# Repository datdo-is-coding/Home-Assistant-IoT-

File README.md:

# HomeCompetition

Ứng dụng Firebase, Gateway Pi4 và các Box ESP32-S3. Bản đồ nguồn đã rà soát ngày
2026-10-28:

| Thành phần | Nguồn duy trì | Điểm vào |
| --- | --- | --- |
| App duy nhất | `App/HomeCompetition/` | `lib/main.dart` → `FirebaseHomeClient` |
| Web Dashboard | `Web/iot_dashboard/` | `app.py` / `lib/main.dart` |
| Gateway chính | `Gateway/gateway/` | `main.py`, cầu nối `firebase_commissioning.py` |
| Đăng ký/quyền/kênh/lệnh Core | `Gateway/gateway/core_v1/` | Registry SQLite, provisioning, command queue |
| OTA đã ký | `Gateway/gateway/fleet_ota/` | `python -m gateway.fleet_ota.local` cho pilot Pi |
| ActionBox 3 relay / 3 BL0942 | `Firmware/firmware_esp/ActionBox_V2/` | `src/main.cpp` |
| SubBox điều phối / âm thanh | `Firmware/firmware_esp/SubBox/` | `src/main.cpp` |
| Giao thức/OTA/bảo mật chung | `Firmware/firmware_esp/common/hc_core/` | Component ESP-IDF của cả hai Box |
| Giọng nói đang dùng | `Gateway/gateway/asr_engine.py`, `core_v1/speaker_voice.py` | Pi4 nhận PCM, ASR, lệnh Core và phản hồi; WakeNet ở ActionBox |
| Model/MFCC KWS đã dừng | `Firmware/firmware_esp/common/kws/` | Giữ lịch sử; không build/chạy LocalKws trên SubBox |

Thông tin đang chạy và các phần chưa nối xong nằm trong
[trạng thái hệ thống](docs/architecture/current_state.md). Bản phát hành đã giữ ở
[`releases/`](releases/README.md). Bản sao cũ, công cụ demo, dữ liệu huấn luyện đã
dừng và build/cache dư nằm trong
[`archive/2026-10-28-cleanup/`](archive/2026-10-28-cleanup/README.md), kèm manifest
hash và vị trí gốc. Archive giữ dữ liệu để phục hồi, không giảm dung lượng đĩa.

## App

```sh
cd App/HomeCompetition
flutter pub get
flutter analyze
flutter test --concurrency=1
flutter build apk --release
```

Giữ Android application ID đã đăng ký Firebase. Sau khi đổi nhánh hoặc khôi phục
cache, chạy `flutter pub get` để tạo lại phần đăng ký native plugin. Xem
[hướng dẫn app](App/HomeCompetition/README.md).

## Web Dashboard

Ứng dụng web dashboard và server Flask phục vụ giao diện:

```sh
cd Web/iot_dashboard
python3 app.py
# Hoặc chạy trực tiếp Flutter Web:
# flutter run -d chrome
```

## Firmware

Trong môi trường ESP-IDF 6.0.2 đã kích hoạt, từ gốc repo:

```sh
idf.py -C Firmware/firmware_esp/ActionBox_V2 build
idf.py -C Firmware/firmware_esp/SubBox build
```

`managed_components/`, `dependencies.lock`, `sdkconfig` và `sdkconfig.defaults`
của hai project được giữ. `build/` sẽ tạo lại khi build. Không dùng firmware
ActionBox đời cũ hoặc simulator để nạp thay cho `ActionBox_V2`.

## Gateway và kiểm thử

Dịch vụ Pi dùng `Gateway/systemd/smarthome-gateway.service`; cấu hình ghép qua
Firebase xem [`Gateway/firebase/README.md`](Gateway/firebase/README.md).
`deployment/`, `MQTT_Server/`, `protocol/`, `Hardware/` và `sound/` vẫn chứa cấu
hình triển khai, hợp đồng, thiết kế điện và tài nguyên được sử dụng.

```sh
PYTHONPATH=Gateway python -m unittest discover -s Gateway/tests -v
python -m unittest discover -s Firmware/tests -v
```

Gateway cần các dependency đã cài; test Firebase Rules cần emulator loopback
riêng theo hướng dẫn trong test. Firmware host tests cần `g++`, `numpy` và Python
của ESP-IDF cho các bài NVS. Mẫu KWS dùng kiểm thử nằm ở
`Firmware/tests/fixtures/kws/`; không cần chạy lại huấn luyện.

`archive/` được loại khỏi tìm kiếm mặc định. Dùng `rg --no-ignore` khi tra cứu
lịch sử. Nguồn Gateway có các module tương thích được main, API hoặc test gọi;
không tách chúng khỏi dịch vụ chỉ vì app hiện dùng Firebase.

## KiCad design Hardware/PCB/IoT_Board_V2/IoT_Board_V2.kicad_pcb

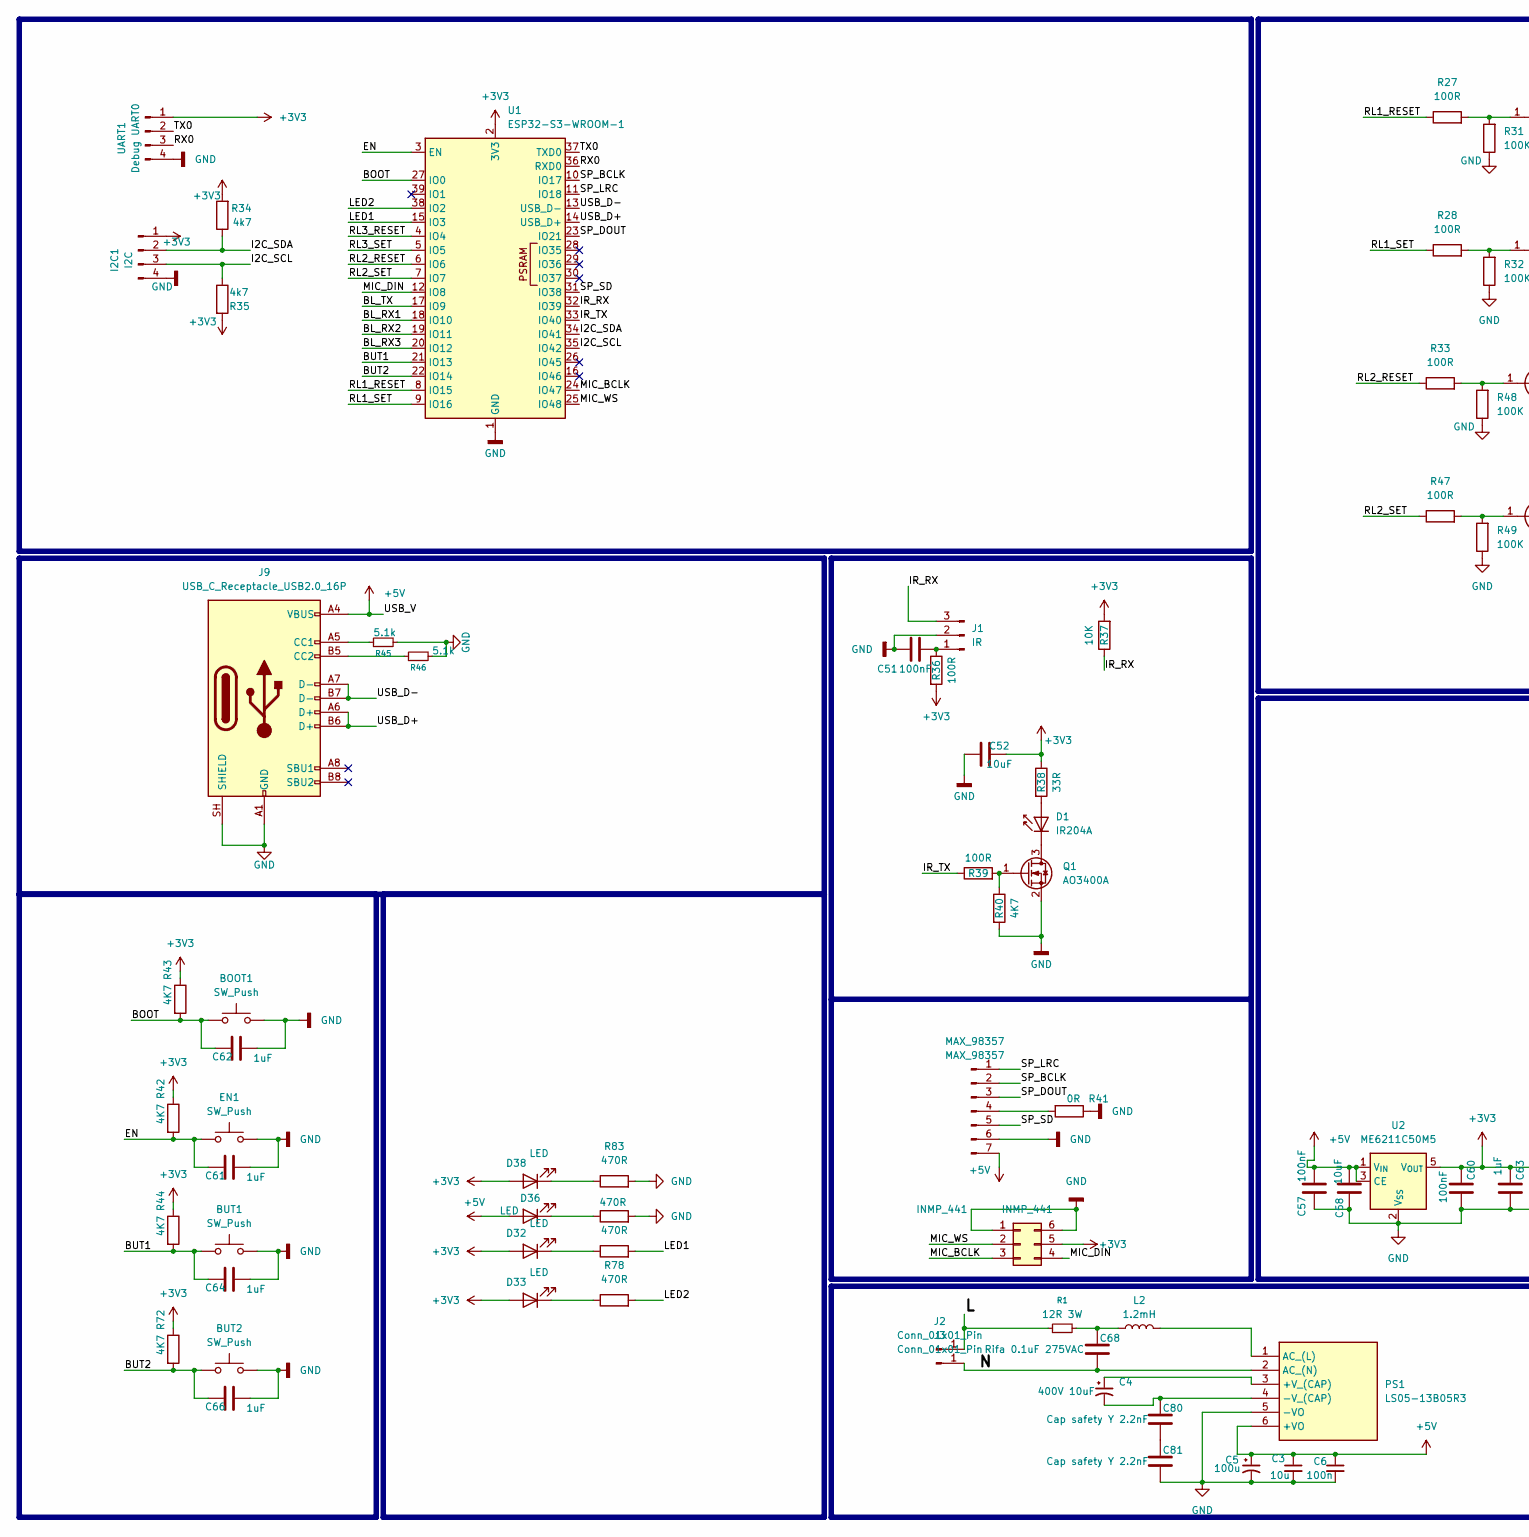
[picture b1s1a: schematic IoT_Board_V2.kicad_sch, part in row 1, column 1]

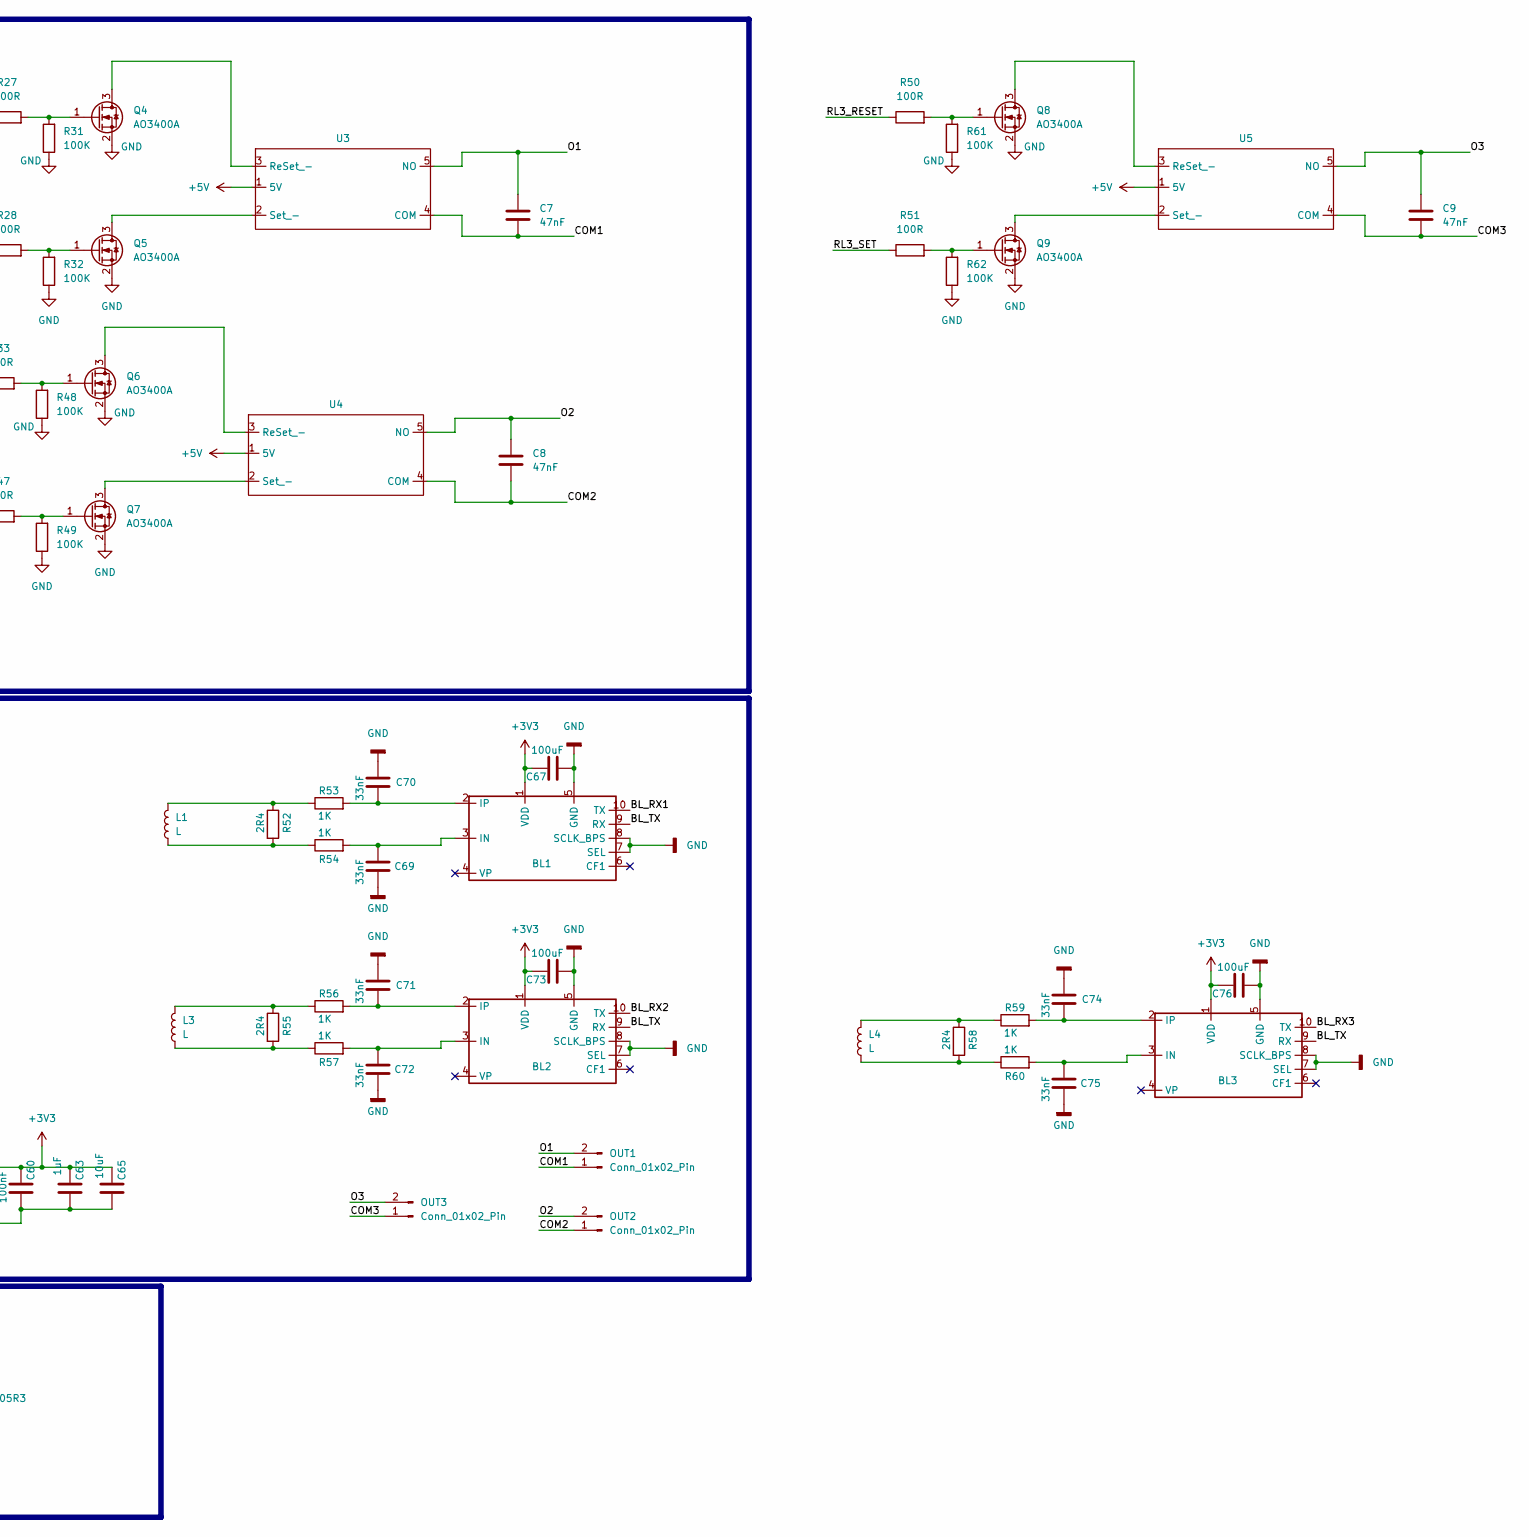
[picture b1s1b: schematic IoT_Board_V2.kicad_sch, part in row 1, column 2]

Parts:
BL1, BL2, BL3: SSOP-10_3.9x4.9mm_P1.00mm
BOOT1: SW_Push; SW_SPST_TL3305A
BUT1, BUT2: SW_Push; SW_SPST_TL3305A
C3: 10u; C_1206_3216Metric
C4: 400V 10uF; CP_Radial_D10.0mm_P5.00mm
C5: 100u; CP_Elec_10x10.5
C6: 100n; C_1206_3216Metric
C7, C8, C9: 47nF; C_Disc_D8.0mm_W5.0mm_P10.00mm
C51: 100nF; R_0805_2012Metric_Pad1.20x1.40mm_HandSolder
C52, C58, C65: 10uF; R_0603_1608Metric_Pad0.98x0.95mm_HandSolder
C57, C60: 100nF; R_0603_1608Metric_Pad0.98x0.95mm_HandSolder
C61, C62, C63, C64, C66: 1uF; R_0603_1608Metric_Pad0.98x0.95mm_HandSolder
C67, C73, C76: 100uF; R_0603_1608Metric_Pad0.98x0.95mm_HandSolder
C68: Rifa 0.1uF 275VAC; C_Rect_L16.5mm_W5.0mm_P15.00mm_MKT
C69, C70, C71, C72, C74, C75: 33nF; R_0603_1608Metric_Pad0.98x0.95mm_HandSolder
C80, C81: Cap safety Y 2.2nF; C_Disc_D10.5mm_W5.0mm_P7.50mm
D1: IR204A; LED_D3.0mm_IRBlack
D32, D33, D36, D38: LED; LED_0805_2012Metric_Pad1.15x1.40mm_HandSolder
EN1: SW_Push; SW_SPST_TL3305A
I2C1: I2C; JST_GH_BM04B-GHS-TBT_1x04-1MP_P1.25mm_Vertical
INMP_441: INMP_441; JST_GH_BM06B-GHS-TBT_1x06-1MP_P1.25mm_Vertical
J1: IR; PinHeader_1x03_P2.54mm_Vertical
J2, J3: Conn_01x01_Pin; Untitled
J9: USB_C_Receptacle_USB2.0_16P; USB_C_Receptacle_HCTL_HC-TYPE-C-16P-01A
L1, L3, L4: L; CT225A4mm
L2: 1.2mH; L_Wuerth_WE-PD-Typ-LS
MAX_98357: MAX_98357; JST_GH_BM07B-GHS-TBT_1x07-1MP_P1.25mm_Vertical
OUT1, OUT2, OUT3: Conn_01x02_Pin; Cos_blade_6.3
PS1: LS05-13B05R3; LS0513B05R3; Manufacturer_Part_Number LS05-13B05R3
Q1, Q4, Q5, Q6, Q7, Q8, Q9: AO3400A; SOT-23
R1: 12R 3W; R_Axial_DIN0309_L9.0mm_D3.2mm_P12.70mm_Horizontal
R27, R28, R33, R36, R39, R47, R50, R51: 100R; R_0603_1608Metric_Pad0.98x0.95mm_HandSolder
R31, R32, R48, R49, R61, R62: 100K; R_0603_1608Metric_Pad0.98x0.95mm_HandSolder
R34, R35: 4k7; R_0603_1608Metric_Pad0.98x0.95mm_HandSolder
R37: 10K; R_0603_1608Metric_Pad0.98x0.95mm_HandSolder
R38: 33R; R_0603_1608Metric_Pad0.98x0.95mm_HandSolder
R40, R42, R43, R44, R72: 4K7; R_0603_1608Metric_Pad0.98x0.95mm_HandSolder
R41: 0R; R_0603_1608Metric_Pad0.98x0.95mm_HandSolder
R45, R46: 5.1k; R_0603_1608Metric_Pad0.98x0.95mm_HandSolder
R52, R55, R58: 2R4; R_0603_1608Metric_Pad0.98x0.95mm_HandSolder
R53, R54, R56, R57, R59, R60: 1K; R_0603_1608Metric_Pad0.98x0.95mm_HandSolder
R77, R78, R81, R83: 470R; R_0603_1608Metric_Pad0.98x0.95mm_HandSolder
U1: ESP32-S3-WROOM-1; ESP32-S3-WROOM-1U
U2: ME6211C50M5; SOT-23-5
U3, U4, U5: HKE3LT ：20A 250VAC TV- 10 250VAC 10A 30VDC
UART1: Debug UART0; PinHeader_1x04_P2.54mm_Vertical

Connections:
+3V3: BL1.1 (VDD), BL2.1 (VDD), BL3.1 (VDD), C52.2, C60.2, C63.2, C65.2, C67.2, C73.2, C76.2, D32.2 (A), D33.2 (A), D38.2 (A), I2C1.1, INMP_441.5, R34.2, R35.2, R36.2, R37.2, R38.1, R42.1, R43.1, R44.1, R72.1, U1.2 (3V3), U2.5 (V_{OUT}), UART1.1
+5V: C3.1, C5.1, C6.1, C57.2, C58.2, D36.2 (A), J9.A4 (VBUS), J9.A9 (VBUS), J9.B4 (VBUS), J9.B9 (VBUS), MAX_98357.7, PS1.6 (+VO), U2.1 (V_{IN}), U2.3 (CE), U3.1 (5V), U4.1 (5V), U5.1 (5V)
/BL_RX1: BL1.10 (TX), U1.18 (IO10)
/BL_RX2: BL2.10 (TX), U1.19 (IO11)
/BL_RX3: BL3.10 (TX), U1.20 (IO12)
/BL_TX: BL1.9 (RX), BL2.9 (RX), BL3.9 (RX), U1.17 (IO9)
/BOOT: BOOT1.1, C62.2, R43.2, U1.27 (IO0)
/BUT1: BUT1.1, C64.2, R44.2, U1.21 (IO13)
/BUT2: BUT2.1, C66.2, R72.2, U1.22 (IO14)
/COM1: C7.2, OUT1.1, U3.4 (COM)
/COM2: C8.2, OUT2.1, U4.4 (COM)
/COM3: C9.2, OUT3.1, U5.4 (COM)
/EN: C61.2, EN1.1, R42.2, U1.3 (EN)
/I2C_SCL: I2C1.3, R35.1, U1.35 (IO42)
/I2C_SDA: I2C1.2, R34.1, U1.34 (IO41)
/IR_RX: J1.3, R37.1, U1.32 (IO39)
/IR_TX: R39.1, U1.33 (IO40)
/L: J2.1 (Pin_1_1), R1.1
/LED1: R77.2, U1.15 (IO3)
/LED2: R78.2, U1.38 (IO2)
/MIC_BCLK: INMP_441.3, U1.24 (IO47)
/MIC_DIN: INMP_441.4, U1.12 (IO8)
/MIC_WS: INMP_441.2, U1.25 (IO48)
/N: C68.2, J3.1 (Pin_1_1), PS1.2 (AC_(N))
/O1: C7.1, OUT1.2, U3.5 (NO)
/O2: C8.1, OUT2.2, U4.5 (NO)
/O3: C9.1, OUT3.2, U5.5 (NO)
/RL1_RESET: R27.1, U1.8 (IO15)
/RL1_SET: R28.1, U1.9 (IO16)
/RL2_RESET: R33.1, U1.6 (IO6)
/RL2_SET: R47.1, U1.7 (IO7)
/RL3_RESET: R50.1, U1.4 (IO4)
/RL3_SET: R51.1, U1.5 (IO5)
/RX0: U1.36 (RXD0), UART1.3
/SP_BCLK: MAX_98357.2, U1.10 (IO17)
/SP_DOUT: MAX_98357.3, U1.23 (IO21)
/SP_LRC: MAX_98357.1, U1.11 (IO18)
/SP_SD: MAX_98357.5, U1.31 (IO38)
/TX0: U1.37 (TXD0), UART1.2
/USB_D+: J9.A6 (D+), J9.B6 (D+), U1.14 (USB_D+)
/USB_D-: J9.A7 (D-), J9.B7 (D-), U1.13 (USB_D-)
GND: BL1.5 (GND), BL1.7 (SEL), BL1.8 (SCLK_BPS), BL2.5 (GND), BL2.7 (SEL), BL2.8 (SCLK_BPS), BL3.5 (GND), BL3.7 (SEL), BL3.8 (SCLK_BPS), BOOT1.2, BUT1.2, BUT2.2, C3.2, C5.2, C6.2, C51.2, C52.1, C57.1, C58.1, C60.1, C61.1, C62.1, C63.1, C64.1, C65.1, C66.1, C67.1, C69.2, C70.1, C71.1, C72.2, C73.1, C74.1, C75.2, C76.1, C81.2, EN1.2, I2C1.4, INMP_441.1, INMP_441.6, J1.2, J9.A1 (GND), J9.A12 (GND), J9.B1 (GND), J9.B12 (GND), J9.SH (SHIELD), MAX_98357.6, PS1.5 (-VO), Q1.2 (S), Q4.2 (S), Q5.2 (S), Q6.2 (S), Q7.2 (S), Q8.2 (S), Q9.2 (S), R31.1, R32.1, R40.2, R41.1, R45.2, R46.2, R48.1, R49.1, R61.1, R62.1, R81.2, R83.2, U1.1 (GND), U1.40 (GND), U1.41 (GND), U2.2 (V_{SS}), UART1.4
unnamed: BL1.3 (IN), C69.1, R54.2
unnamed: BL1.2 (IP), C70.2, R53.2
unnamed: BL2.3 (IN), C72.1, R57.2
unnamed: BL2.2 (IP), C71.2, R56.2
unnamed: BL3.3 (IN), C75.1, R60.2
unnamed: BL3.2 (IP), C74.2, R59.2
unnamed: C68.1, L2.1, R1.2
unnamed: C80.2, C81.1
unnamed: D1.2 (A), R38.2
unnamed: D1.1 (K), Q1.3 (D)
unnamed: D32.1 (K), R77.1
unnamed: D33.1 (K), R78.1
unnamed: D36.1 (K), R81.1
unnamed: D38.1 (K), R83.1
unnamed: C51.1, J1.1, R36.1
unnamed: J9.A5 (CC1), R45.1
unnamed: J9.B5 (CC2), R46.1
unnamed: L1.1, R52.2, R54.1
unnamed: L1.2, R52.1, R53.1
unnamed: L3.1, R55.2, R57.1
unnamed: L3.2, R55.1, R56.1
unnamed: L4.1, R58.2, R60.1
unnamed: L4.2, R58.1, R59.1
unnamed: MAX_98357.4, R41.2
unnamed: C4.1, PS1.3 (+V_(CAP))
unnamed: C4.2, C80.1, PS1.4 (-V_(CAP))
unnamed: L2.2, PS1.1 (AC_(L))
unnamed: Q1.1 (G), R39.2, R40.1
unnamed: Q4.3 (D), U3.3 (ReSet_-)
unnamed: Q4.1 (G), R27.2, R31.2
unnamed: Q5.3 (D), U3.2 (Set_-)
unnamed: Q5.1 (G), R28.2, R32.2
unnamed: Q6.3 (D), U4.3 (ReSet_-)
unnamed: Q6.1 (G), R33.2, R48.2
unnamed: Q7.3 (D), U4.2 (Set_-)
unnamed: Q7.1 (G), R47.2, R49.2
unnamed: Q8.3 (D), U5.3 (ReSet_-)
unnamed: Q8.1 (G), R50.2, R61.2
unnamed: Q9.3 (D), U5.2 (Set_-)
unnamed: Q9.1 (G), R51.2, R62.2

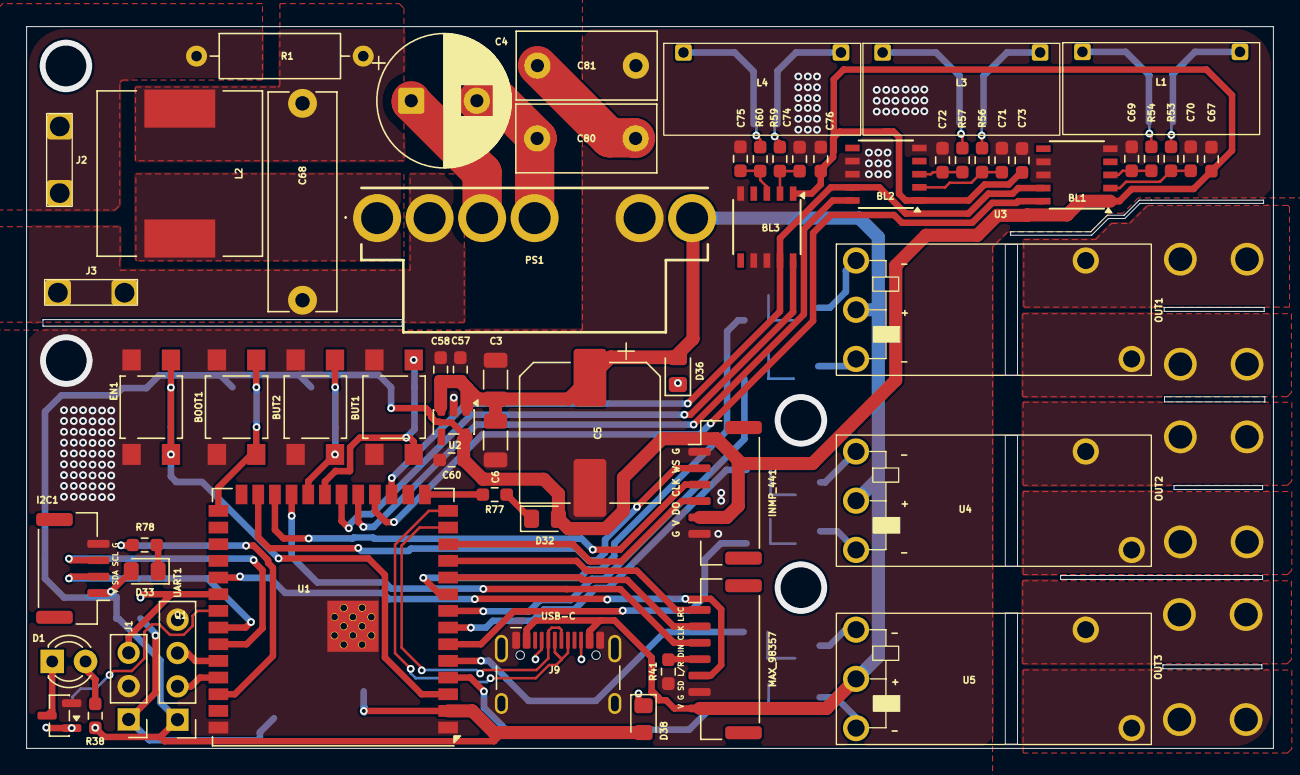
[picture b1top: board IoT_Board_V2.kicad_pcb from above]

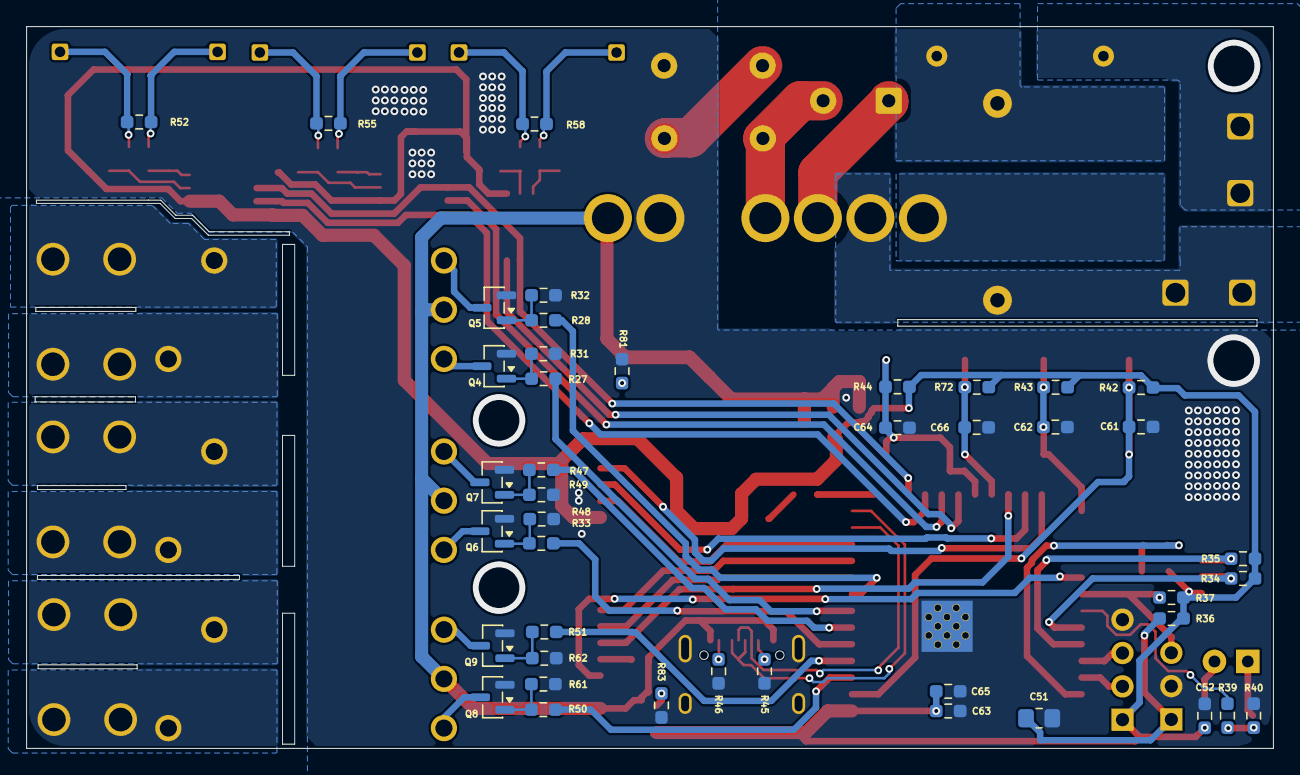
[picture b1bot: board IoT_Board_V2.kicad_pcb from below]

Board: 2 copper layers, 95.0 x 55.0 mm, 107 parts (43 on the bottom side), 82 nets.

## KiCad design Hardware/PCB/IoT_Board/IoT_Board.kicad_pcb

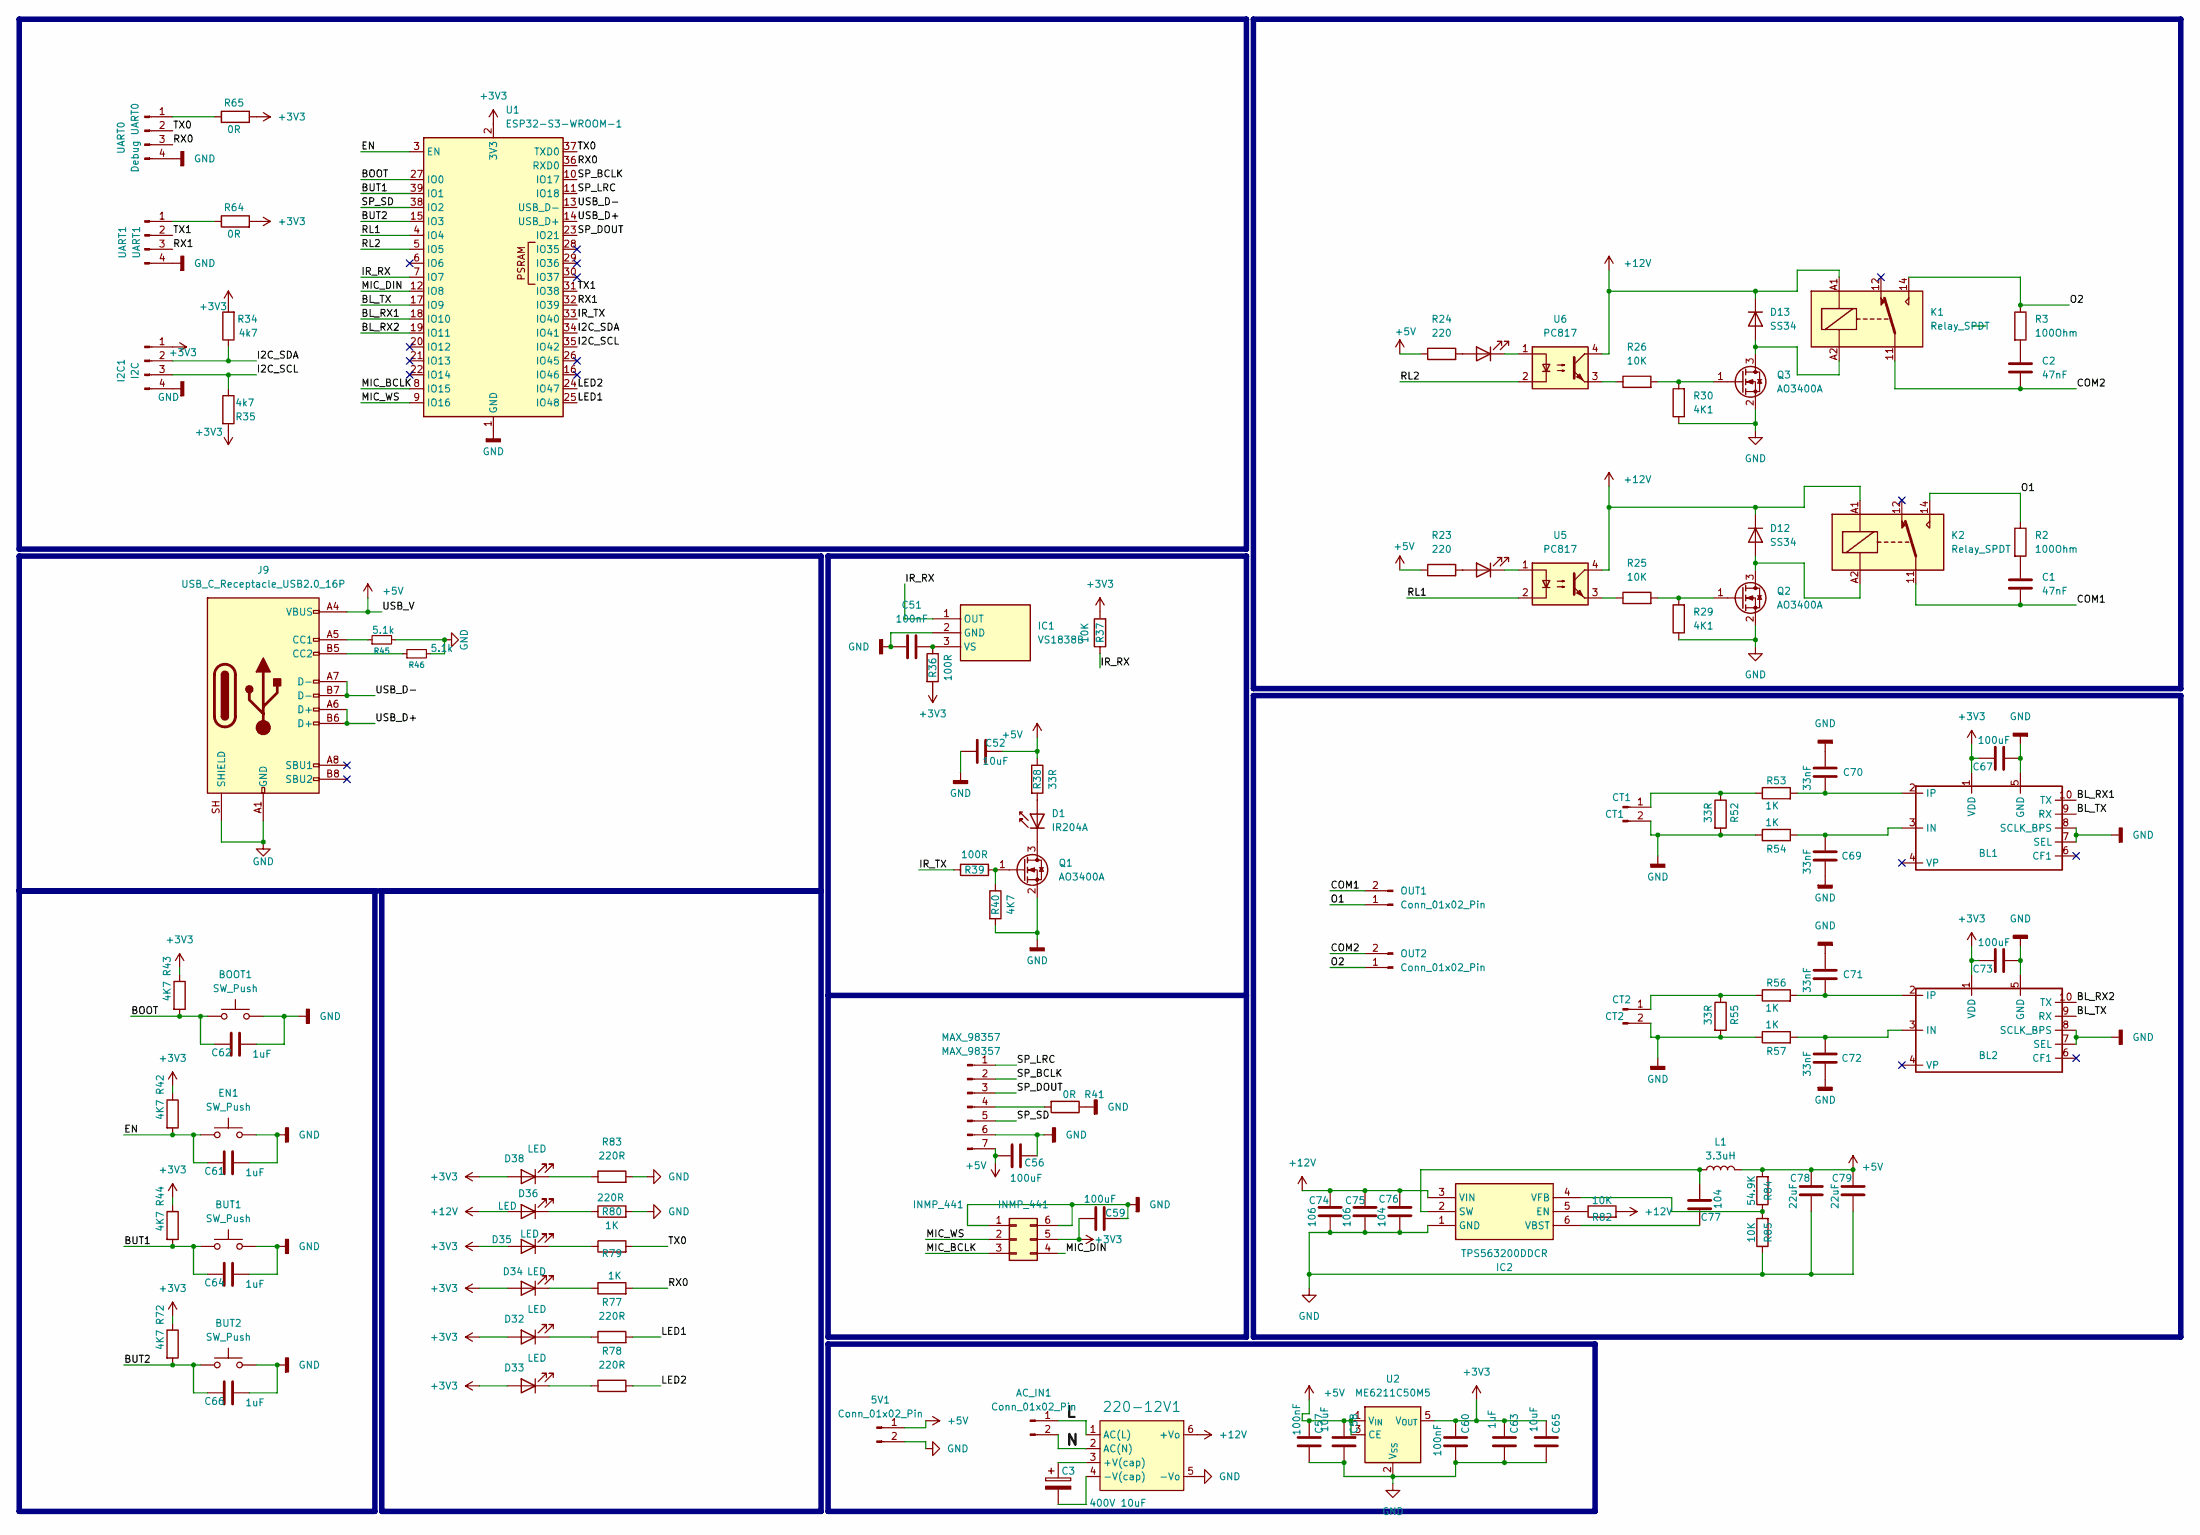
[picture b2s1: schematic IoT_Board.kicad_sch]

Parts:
5V1: Conn_01x02_Pin; PinHeader_1x02_P2.54mm_Vertical
220-12V1: LS05_12V; LS05-23BxxDR3
AC_IN1: Conn_01x02_Pin; TerminalBlock_Phoenix_MKDS-1,5-2-5.08_1x02_P5.08mm_Horizont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
BL1, BL2: SSOP-10_3.9x4.9mm_P1.00mm
BOOT1: SW_Push; SW_Tactile_SPST_NO_Straight_CK_PTS636Sx25SMTRLFS
BUT1, BUT2: SW_Push; SW_Tactile_SPST_NO_Straight_CK_PTS636Sx25SMTRLFS
C1, C2: 47nF; C_Disc_D10.5mm_W5.0mm_P7.50mm
C3: 400V 10uF; CP_Elec_10x10.5
C51: 100nF; R_0805_2012Metric_Pad1.20x1.40mm_HandSolder
C52, C58, C65: 10uF; R_0603_1608Metric_Pad0.98x0.95mm_HandSolder
C56, C59, C67, C73: 100uF; R_0603_1608Metric_Pad0.98x0.95mm_HandSolder
C57, C60: 100nF; R_0603_1608Metric_Pad0.98x0.95mm_HandSolder
C61, C62, C63, C64, C66: 1uF; R_0603_1608Metric_Pad0.98x0.95mm_HandSolder
C69, C70, C71, C72: 33nF; R_0603_1608Metric_Pad0.98x0.95mm_HandSolder
C74, C75: 106; R_1206_3216Metric_Pad1.30x1.75mm_HandSolder
C76, C77: 104; R_0603_1608Metric_Pad0.98x0.95mm_HandSolder
C78, C79: 22uF; R_0603_1608Metric_Pad0.98x0.95mm_HandSolder
CT1: CT1; JST_XH_B2B-XH-A_1x02_P2.50mm_Vertical
CT2: CT2; JST_XH_B2B-XH-A_1x02_P2.50mm_Vertical
D1: IR204A; LED_D3.0mm_IRBlack
D12, D13: SS34; D_SMA_Handsoldering
D32, D33, D34, D35, D36, D38: LED; LED_0805_2012Metric_Pad1.15x1.40mm_HandSolder
EN1: SW_Push; SW_Tactile_SPST_NO_Straight_CK_PTS636Sx25SMTRLFS
I2C1: I2C; JST_XH_B4B-XH-A_1x04_P2.50mm_Vertical
IC1: VS1838B; Manufacturer_Part_Number VS1838B
IC2: TPS563200DDCR; SOT95P280X110-6N; Manufacturer_Part_Number TPS563200DDCR; Mouser Part Number 595-TPS563200DDCR
INMP_441: INMP_441; PinHeader_2x03_P2.54mm_Vertical
J9: USB_C_Receptacle_USB2.0_16P; USB_C_Receptacle_HCTL_HC-TYPE-C-16P-01A
K1, K2: Relay_SPDT; Relay_SPDT_Schrack-RT1-16A-FormC_RM5mm
L1: 3.3uH; L_7.3x7.3_H3.5
LED_RL1, LED_RL2: LED; LED_0805_2012Metric_Pad1.15x1.40mm_HandSolder
MAX_98357: MAX_98357; PinHeader_1x07_P2.54mm_Vertical
OUT1, OUT2: Conn_01x02_Pin; TerminalBlock_Phoenix_MKDS-1,5-2-5.08_1x02_P5.08mm_Horizont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
Q1, Q2, Q3: AO3400A; SOT-23
R2, R3: 100Ohm; R_Axial_DIN0414_L11.9mm_D4.5mm_P15.24mm_Horizontal
R23, R24: 220; R_0603_1608Metric_Pad0.98x0.95mm_HandSolder
R25, R26, R37, R82, R85: 10K; R_0603_1608Metric_Pad0.98x0.95mm_HandSolder
R29, R30: 4K1; R_0603_1608Metric_Pad0.98x0.95mm_HandSolder
R34, R35: 4k7; R_0603_1608Metric_Pad0.98x0.95mm_HandSolder
R36, R39: 100R; R_0603_1608Metric_Pad0.98x0.95mm_HandSolder
R38, R52, R55: 33R; R_0603_1608Metric_Pad0.98x0.95mm_HandSolder
R40, R42, R43, R44, R72: 4K7; R_0603_1608Metric_Pad0.98x0.95mm_HandSolder
R41, R64, R65: 0R; R_0603_1608Metric_Pad0.98x0.95mm_HandSolder
R45, R46: 5.1k; R_0603_1608Metric_Pad0.98x0.95mm_HandSolder
R53, R54, R56, R57, R79, R80: 1K; R_0603_1608Metric_Pad0.98x0.95mm_HandSolder
R77, R78, R81, R83: 220R; R_0603_1608Metric_Pad0.98x0.95mm_HandSolder
R84: 54.9K; R_0603_1608Metric_Pad0.98x0.95mm_HandSolder
U1: ESP32-S3-WROOM-1; ESP32-S3-WROOM-1U
U2: ME6211C50M5; SOT-23-5
U5, U6: PC817; SOP254P960X420-4N
UART0: Debug UART0; JST_XH_B4B-XH-A_1x04_P2.50mm_Vertical
UART1: UART1; JST_XH_B4B-XH-A_1x04_P2.50mm_Vertical

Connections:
+3V3: BL1.1 (VDD), BL2.1 (VDD), C59.1, C60.2, C63.2, C65.2, C67.2, C73.2, D32.2 (A), D33.2 (A), D34.2 (A), D35.2 (A), D38.2 (A), I2C1.1, INMP_441.5, R34.2, R35.2, R36.2, R37.2, R42.1, R43.1, R44.1, R64.2, R65.2, R72.1, U1.2 (3V3), U2.5 (V_{OUT})
+5V: 5V1.1, C52.2, C56.1, C57.2, C58.2, C78.1, C79.1, J9.A4 (VBUS), J9.A9 (VBUS), J9.B4 (VBUS), J9.B9 (VBUS), L1.2, MAX_98357.7, R23.1, R24.1, R38.1, R84.2, U2.1 (V_{IN}), U2.3 (CE)
+12V: 220-12V1.6 (+Vo), C74.1, C75.1, C76.1, D12.1 (K), D13.1 (K), D36.2 (A), IC2.3 (VIN), K1.A1, K2.A1, R82.2, U5.4, U6.4
/BL_RX1: BL1.10 (TX), U1.18 (IO10)
/BL_RX2: BL2.6 (CF1), BL2.10 (TX), U1.19 (IO11)
/BL_TX: BL1.9 (RX), BL2.9 (RX), U1.17 (IO9)
/BOOT: BOOT1.1, C62.2, R43.2, U1.27 (IO0)
/BUT1: BUT1.1, C64.2, R44.2, U1.39 (IO1)
/BUT2: BUT2.1, C66.2, R72.2, U1.15 (IO3)
/COM1: C1.2, K2.11, OUT1.2
/COM2: C2.2, K1.11, OUT2.2
/EN: C61.2, EN1.1, R42.2, U1.3 (EN)
/I2C_SCL: I2C1.3, R35.1, U1.35 (IO42)
/I2C_SDA: I2C1.2, R34.1, U1.34 (IO41)
/IR_RX: IC1.1 (OUT), R37.1, U1.7 (IO7)
/IR_TX: R39.1, U1.33 (IO40)
/L: 220-12V1.1 (AC(L)), AC_IN1.1
/LED1: R77.2, U1.25 (IO48)
/LED2: R78.2, U1.24 (IO47)
/MIC_BCLK: INMP_441.3, U1.8 (IO15)
/MIC_DIN: INMP_441.4, U1.12 (IO8)
/MIC_WS: INMP_441.2, U1.9 (IO16)
/N: 220-12V1.2 (AC(N)), AC_IN1.2
/O1: K2.14, OUT1.1, R2.1
/O2: K1.14, OUT2.1, R3.1
/RL1: U1.4 (IO4), U5.2
/RL2: U1.5 (IO5), U6.2
/RX0: R79.2, U1.36 (RXD0), UART0.3
/RX1: U1.32 (IO39), UART1.3
/SP_BCLK: MAX_98357.2, U1.10 (IO17)
/SP_DOUT: MAX_98357.3, U1.23 (IO21)
/SP_LRC: MAX_98357.1, U1.11 (IO18)
/SP_SD: MAX_98357.5, U1.38 (IO2)
/TX0: R80.2, U1.37 (TXD0), UART0.2
/TX1: U1.31 (IO38), UART1.2
/USB_D+: J9.A6 (D+), J9.B6 (D+), U1.14 (USB_D+)
/USB_D-: J9.A7 (D-), J9.B7 (D-), U1.13 (USB_D-)
GND: 5V1.2, 220-12V1.5 (-Vo), BL1.5 (GND), BL1.7 (SEL), BL1.8 (SCLK_BPS), BL2.5 (GND), BL2.7 (SEL), BL2.8 (SCLK_BPS), BOOT1.2, BUT1.2, BUT2.2, C51.2, C52.1, C56.2, C57.1, C58.1, C59.2, C60.1, C61.1, C62.1, C63.1, C64.1, C65.1, C66.1, C67.1, C69.2, C70.1, C71.1, C72.2, C73.1, C74.2, C75.2, C76.2, C78.2, C79.2, CT1.2, CT2.2, EN1.2, I2C1.4, IC1.2 (GND), IC2.1 (GND), INMP_441.1, INMP_441.6, J9.A1 (GND), J9.A12 (GND), J9.B1 (GND), J9.B12 (GND), J9.SH (SHIELD), MAX_98357.6, Q1.2 (S), Q2.2 (S), Q3.2 (S), R29.1, R30.1, R40.2, R41.1, R45.2, R46.2, R52.2, R54.1, R55.2, R57.1, R81.2, R83.2, R85.1, U1.1 (GND), U1.40 (GND), U1.41 (GND), U2.2 (V_{SS}), UART0.4, UART1.4
unnamed: 220-12V1.3 (+V(cap)), C3.1
unnamed: 220-12V1.4 (-V(cap)), C3.2
unnamed: BL1.3 (IN), C69.1, R54.2
unnamed: BL1.2 (IP), C70.2, R53.2
unnamed: BL2.3 (IN), C72.1, R57.2
unnamed: BL2.2 (IP), C71.2, R56.2
unnamed: C1.1, R2.2
unnamed: C2.1, R3.2
unnamed: CT1.1, R52.1, R53.1
unnamed: CT2.1, R55.1, R56.1
unnamed: D1.2 (A), R38.2
unnamed: D1.1 (K), Q1.3 (D)
unnamed: D12.2 (A), K2.A2, Q2.3 (D)
unnamed: D13.2 (A), K1.A2, Q3.3 (D)
unnamed: D32.1 (K), R77.1
unnamed: D33.1 (K), R78.1
unnamed: D34.1 (K), R79.1
unnamed: D35.1 (K), R80.1
unnamed: D36.1 (K), R81.1
unnamed: D38.1 (K), R83.1
unnamed: C51.1, IC1.3 (VS), R36.1
unnamed: IC2.5 (EN), R82.1
unnamed: C77.2, IC2.2 (SW), L1.1
unnamed: C77.1, IC2.6 (VBST)
unnamed: IC2.4 (VFB), R84.1, R85.2
unnamed: J9.A5 (CC1), R45.1
unnamed: J9.B5 (CC2), R46.1
unnamed: LED_RL1.2 (A), R23.2
unnamed: LED_RL1.1 (K), U5.1
unnamed: LED_RL2.2 (A), R24.2
unnamed: LED_RL2.1 (K), U6.1
unnamed: MAX_98357.4, R41.2
unnamed: Q1.1 (G), R39.2, R40.1
unnamed: Q2.1 (G), R25.2, R29.2
unnamed: Q3.1 (G), R26.2, R30.2
unnamed: R25.1, U5.3
unnamed: R26.1, U6.3
unnamed: R65.1, UART0.1
unnamed: R64.1, UART1.1

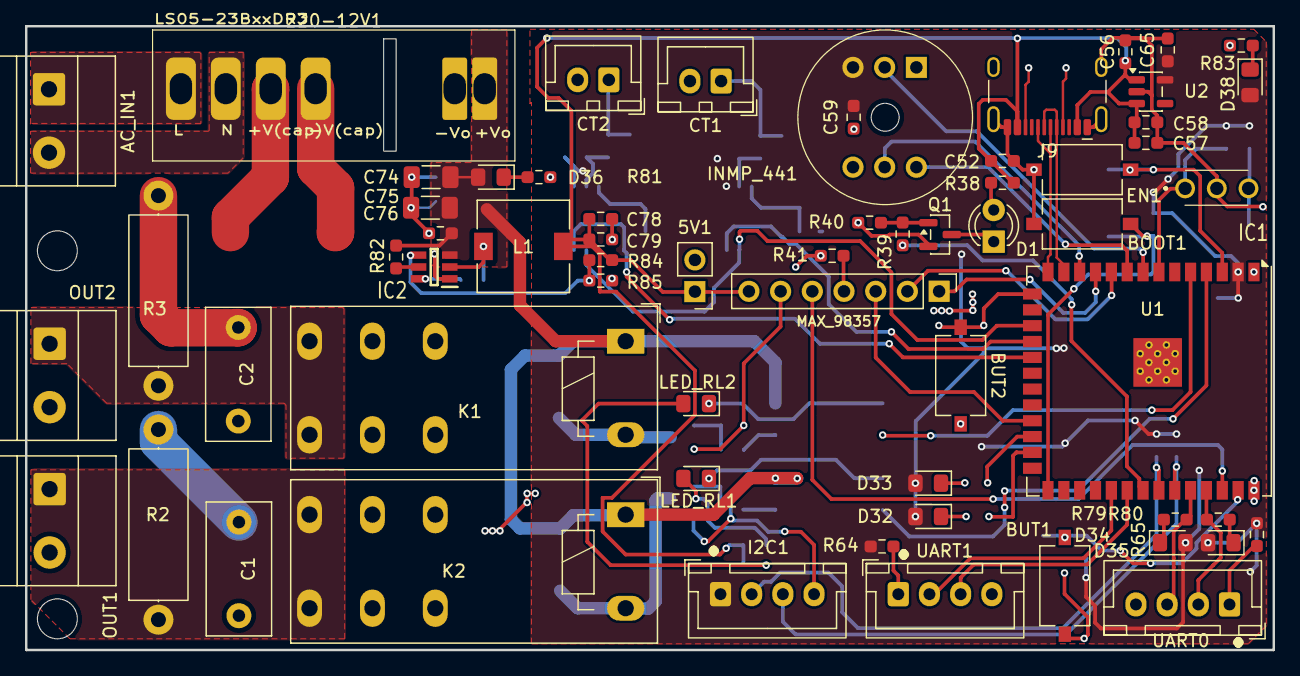
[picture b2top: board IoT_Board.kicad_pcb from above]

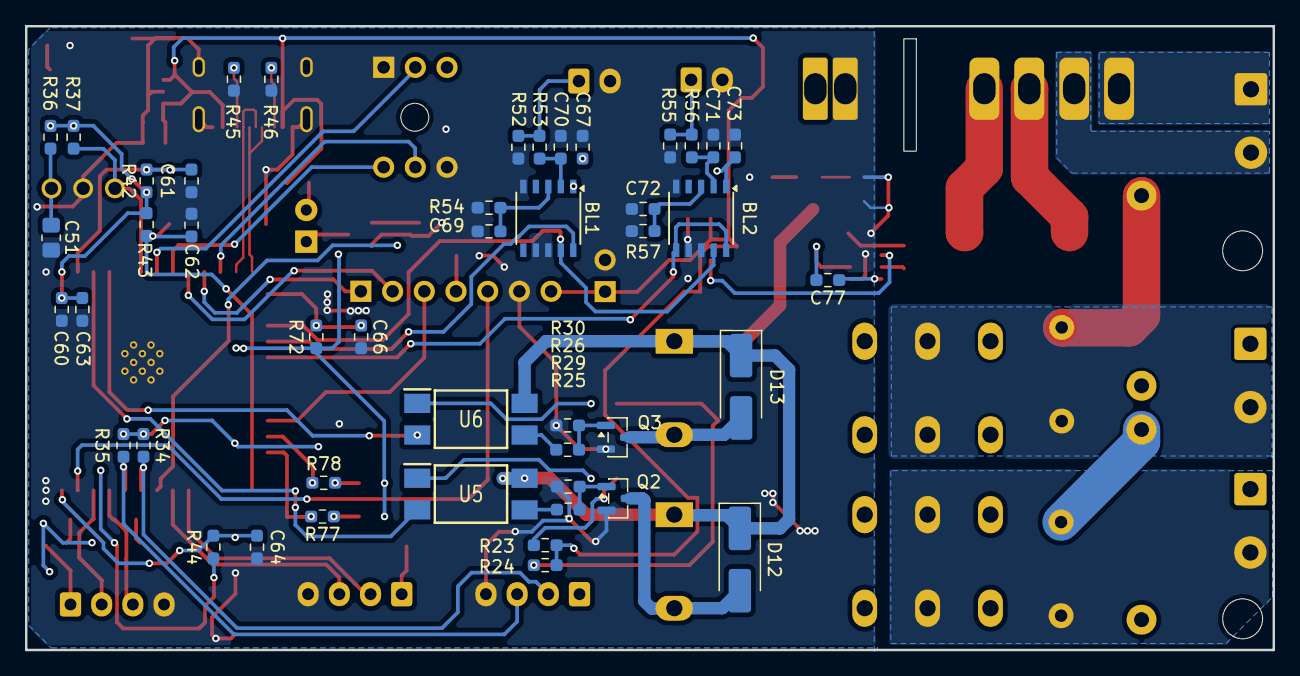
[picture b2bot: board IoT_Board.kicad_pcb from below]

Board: 2 copper layers, 100.0 x 50.0 mm, 108 parts (46 on the bottom side), 75 nets.
